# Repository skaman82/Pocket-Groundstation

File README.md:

# Pocket-Groundstation
The Pocket-Groundstation is a mini ground station that will accept any Fatshark module.</br> 
<strong>Project updates</strong> > https://github.com/skaman82/Pocket-Groundstation/blob/master/updates.md

<b>Features:</b></br>
• takes 2S to 4S voltage</br>
• 3,5mm AV output</br>
• RJ45 output for power+AV (only one wire to goggles) - constant 8V output on any power source </br>
• Powerswitch</br>
• Build-in DVR</br>
• Automatical switching between DVR output (to adjust settings or review footage) or direct module output</br>
• Low-voltage alarm and cell autodetection (adjustable via OLED, so it can work with lipo or li-ion batteries)</br>
• DRV-control via OLED (Eachine Pro DVR)</br>
• RSSI/Channel-information and DVR-Autostart (only with True-D module with 3.7D firmware)</br>
</br>

If you want to join the project or contribute, you are very welcome to do so!</br></br>

<b>Parts:</b></br>
• 3D-Printed Parts </br>
or order them here: </br>
https://www.shapeways.com/product/CZG7FD8B4/pocketgroundstation-module-insert</br>
https://www.shapeways.com/product/DPKJJELEF/pocketgroundstation-case-side-cover</br>
https://www.shapeways.com/product/GCXG232QY/pocketgroundstation-case</br>
</br>
</br>
• PCBs (you can order them with the provided Gerber files in the PCB Folder at http://jlcpcb.com or other vendors) </br>
• M3 inserts (https://de.aliexpress.com/item/100-teile-los-messingeinsatz-M2-M2-5-M3-Durch-gewinde-messing-gewindebuchse-r-ndelmuttern-f-r/32840519444.html) </br>
• Tripod 1/4" Insert: (https://de.aliexpress.com/item/20Pcs-M3-M4-M5-M6-M8-Zinc-Plated-Carbon-Steel-Knurled-Nuts-Rivnut-Flat-Head-Threaded/32812028855.html)</br>
• Eachine PRO DVR </br>
• Arduino Pro Mini (https://de.aliexpress.com/item/1PCS-new-version-1pcs-ATMEGA328P-Pro-Mini-328-Mini-ATMEGA328-5V-16MHz-for-arduino/32830465958.html?spm=a2g0s.9042311.0.0.30d64c4d7417Km)</br>
• 5V Buzzer</br>
• 3-35V to 1.2-30V Step up/down (https://de.aliexpress.com/item/DC-DC-Auto-Boost-Buck-Step-Up-Step-Down-Converter-Module-Solar-Voltage-LM2577-Module/32829391285.html?spm=a2g0s.9042311.0.0.758f4c4daLX5db)</br>
• DC 5.5x2.5 PCB socket (https://de.aliexpress.com/item/10pcs-DC-005-Black-DC-Power-Jack-Socket-Connector-DC005-5-5-2-1mm-2-1/32361314769.html)</br>
• 3.5mm PCB socket (PJ-320D) (https://de.aliexpress.com/item/10pcs-lot-3-5-headphone-jack-audio-jack-PJ-320D-4-pin-SMD-MP3-Accessories-PJ320D/32439357849.html)</br>
• RJ45 PCB socket (RJ45 MOLEX 0446200002/RJ45 MOLEX 0446200001)</br>
• I2C OLED Display 1.3" (https://de.aliexpress.com/item/1-3-Inch-1-3-White-OLED-LCD-4PIN-Display-Module-IIC-I2C-Interface-128x64-for/32837066822.html?spm=a2g0s.9042311.0.0.758f4c4daLX5db)</br>
• PWM video switch (https://de.aliexpress.com/item/2015-Mini-2-Ways-Video-Switcher-Module-2-Channels-Video-Switch-Unit-for-FPV/32552115472.html?spm=a2g0s.9042311.0.0.27424c4dOGX5bp)</br>
• Diode (SMD S1A)</br>
• Resistors 1206 (4.7K / 18K / 220 Ohm)</br>
• Red 3mm LED</br>
• Tactile buttons (3x) (https://de.aliexpress.com/item/100-st-cke-6-6-7mm-Licht-touch-schalter-DIP4-ON-OFF-Tactile-Push-button-micro/32846526815.html?spm=a2g0s.9042311.0.0.758f4c4daLX5db)</br>
• Power switch (https://de.aliexpress.com/item/10Pcs-AC-125V-12A-250V-10A-SPST-2-Pin-2-Position-Mini-Marine-Boat-Switches-Rocker/32830066263.html?spm=a2g0s.9042311.0.0.27424c4dOGX5bp)</br>
• 5V 2A BEC (Diatone)</br>
• RJ45 TBS Tango Cable </br>
• Optional: 3.5mm AV Cable</br>
• Optional: Capacitator (470uF 25V)</br>

# The Build

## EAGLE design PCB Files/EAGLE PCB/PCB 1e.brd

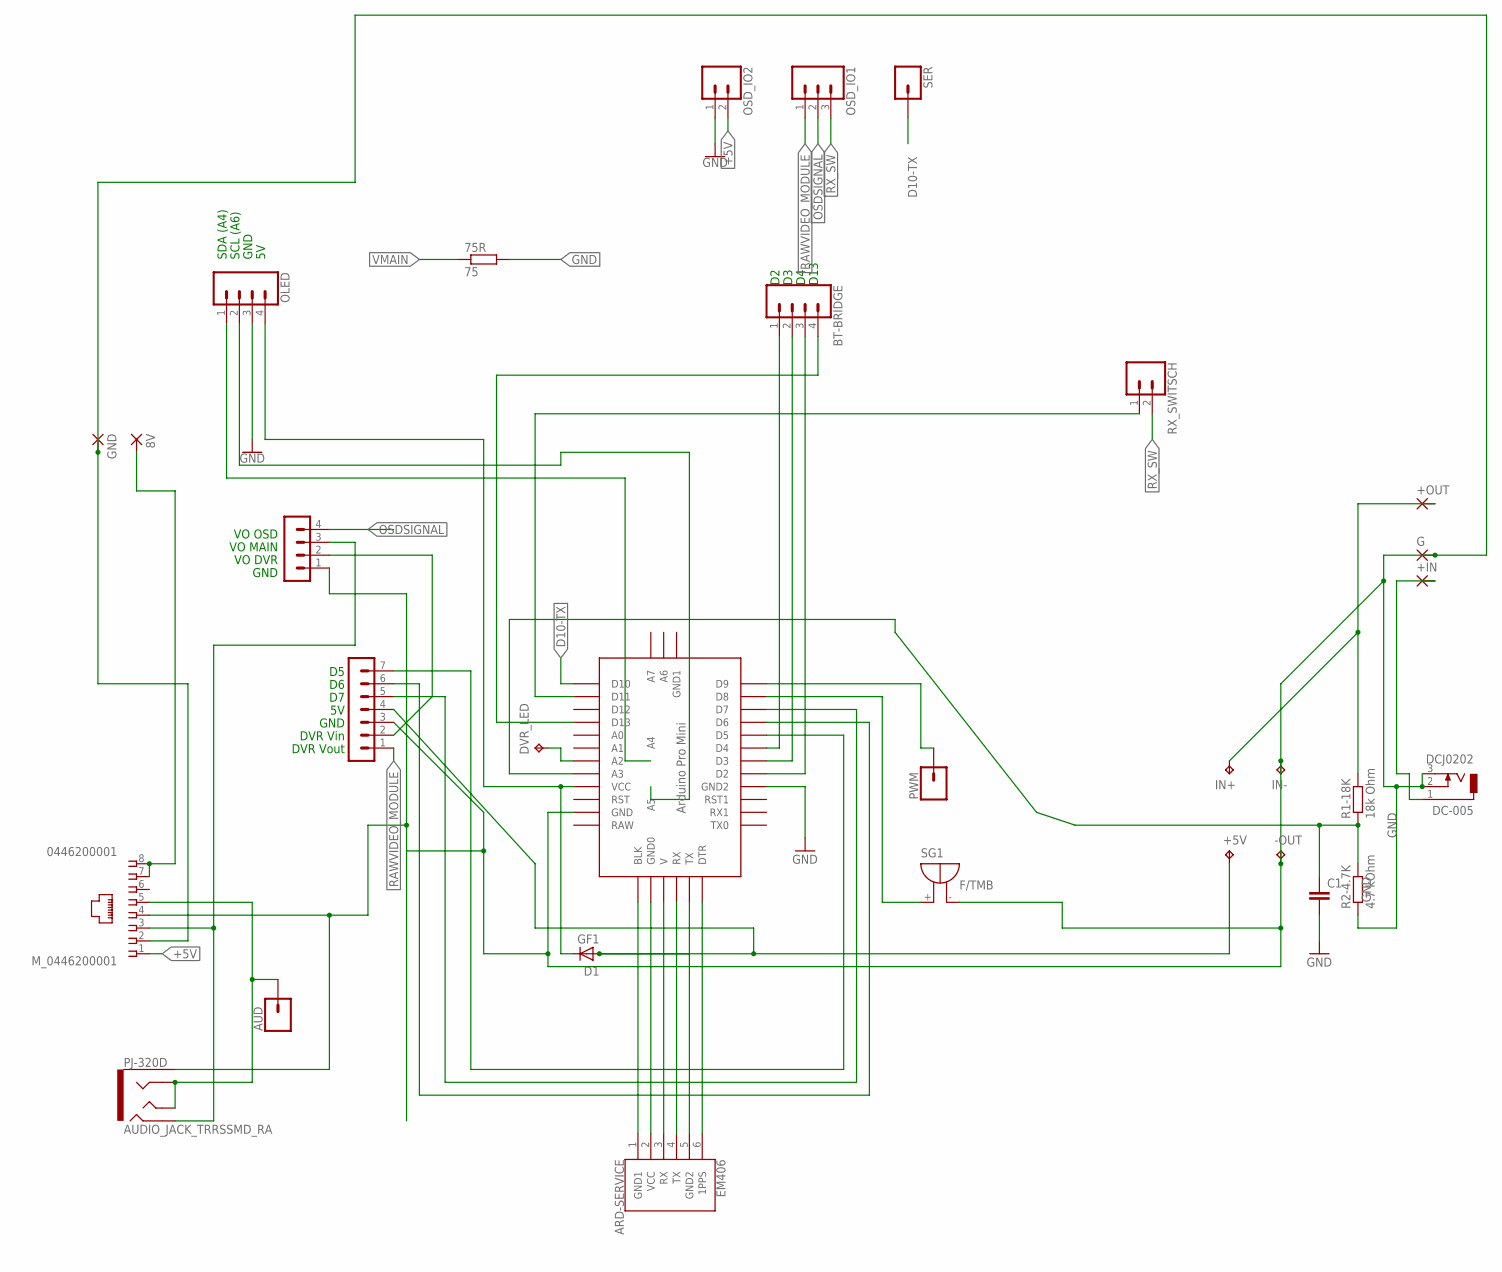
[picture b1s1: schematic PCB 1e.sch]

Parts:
8V: 2,54/1,1
75R: 75; R0603
+5V: TPTP20SQ; TP20SQ
+IN: 2,54/1,1
+OUT: 2,54/1,1
-OUT: TPTP20SQ; TP20SQ
ARD-SERVICE: EM406; 1X06-1MM
AUD: CONN_01; 1X01
BT-BRIDGE: CONN_04; 1X04
C1: C-EUC1206K; C1206K
D1: GF1; SMA-DO214AC
DC-005: DCJ0202
DVR_LED: TPTP20SQ; TP20SQ
G: 2,54/1,1
GND: 2,54/1,1
IN+: TPTP20SQ; TP20SQ
IN-: TPTP20SQ; TP20SQ
MODULE-IO: MA07-1
M_0446200001: 0446200001
OLED: CONN_04; 1X04
OSD_IO1: CONN_03; 1X03
OSD_IO2: CONN_02; 1X02
PJ-320D: AUDIO_JACK_TRRSSMD_RA; AUDIO_JACK_3.5MM_TRRS_SMD_RA
PWM: CONN_01; 1X01
R1-18K: 18k Ohm; M1206
R2-4.7K: 4.7 kOhm; M1206
RX_SWITSCH: CONN_02; 1X02
SER: CONN_01; 1X01
SG1: F/TMB
U$1: ABK-PRO-MINI
V-IO: MA04-1

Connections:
5VPROTECTED: D1.K (C), OLED.4, U$1.VCC
8V: 8V.1, M_0446200001.7, M_0446200001.8
+: +IN.1, DC-005.1
+5V: +5V.TP, D1.A, MODULE-IO.4, M_0446200001.1, OSD_IO2.2
AUDIO: AUD.1, M_0446200001.5, PJ-320D.RING1, PJ-320D.TIP
BUTTON1: BT-BRIDGE.3, U$1.D2
BUTTON2: BT-BRIDGE.2, U$1.D3
BUTTON3: BT-BRIDGE.1, U$1.D4
BUZZER: SG1.+, U$1.D8
D5: MODULE-IO.7, U$1.D5
D6: MODULE-IO.6, U$1.D6
D7: MODULE-IO.5, U$1.D7
D9PWM: PWM.1, U$1.D9
D10-TX: SER.1, U$1.D10
D11-RX: RX_SWITSCH.1, U$1.D11
DVRVIDEO-IN: MODULE-IO.2, V-IO.2
GND: 75R.2, -OUT.TP, C1.2, DC-005.2, DC-005.3, G.1, GND.1, IN-.TP, MODULE-IO.3, M_0446200001.2, M_0446200001.4, OLED.3, OSD_IO2.1, PJ-320D.EARTH, R2-4.7K.1, SG1.-, U$1.GND, U$1.GND1 (GND2), V-IO.1
LED: BT-BRIDGE.4, U$1.D13
unnamed: DVR_LED.TP, U$1.A1 (A2)
unnamed: ARD-SERVICE.1 (GND1), U$1.BLK
unnamed: ARD-SERVICE.2 (VCC), U$1.G (GND0)
unnamed: ARD-SERVICE.3 (RX), U$1.5V (V)
unnamed: ARD-SERVICE.5 (GND2), U$1.TX01 (TX)
unnamed: ARD-SERVICE.6 (1PPS), U$1.DTR
OSDSIGNAL: OSD_IO1.2, V-IO.4
RAWVIDEO_MODULE: MODULE-IO.1, OSD_IO1.1
RX_SW: OSD_IO1.3, RX_SWITSCH.2
SCL: OLED.2, U$1.A5
SDA: OLED.1, U$1.A4
V: ARD-SERVICE.4 (TX), U$1.RX01 (RX)
VCC: +OUT.1, IN+.TP, R1-18K.2
VMAIN: 75R.1, M_0446200001.3, PJ-320D.RING2, V-IO.3
VSENS: C1.1, R1-18K.1, R2-4.7K.2, U$1.A0 (A3)

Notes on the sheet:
VO OSD
VO MAIN
VO DVR
GND
DVR Vin
DVR Vout
SDA (A4)
SCL (A6)
D13

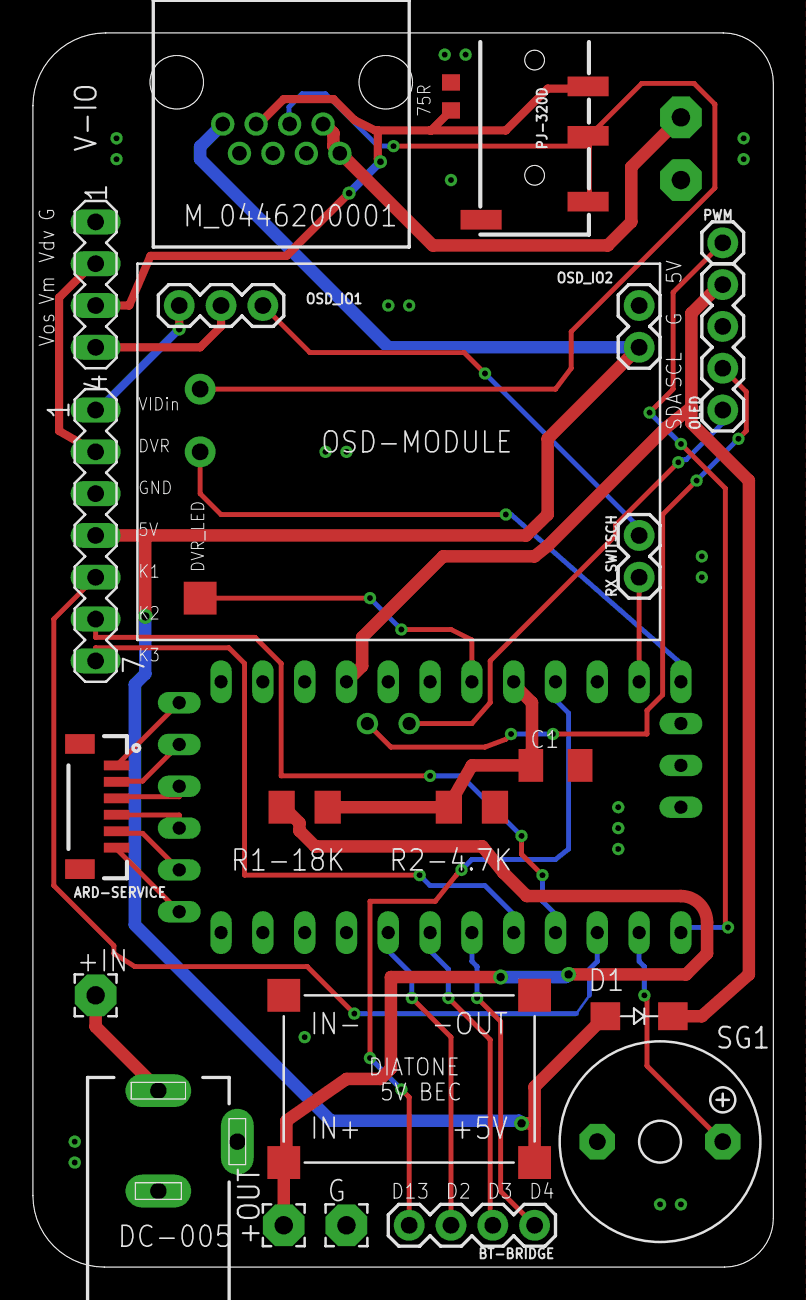
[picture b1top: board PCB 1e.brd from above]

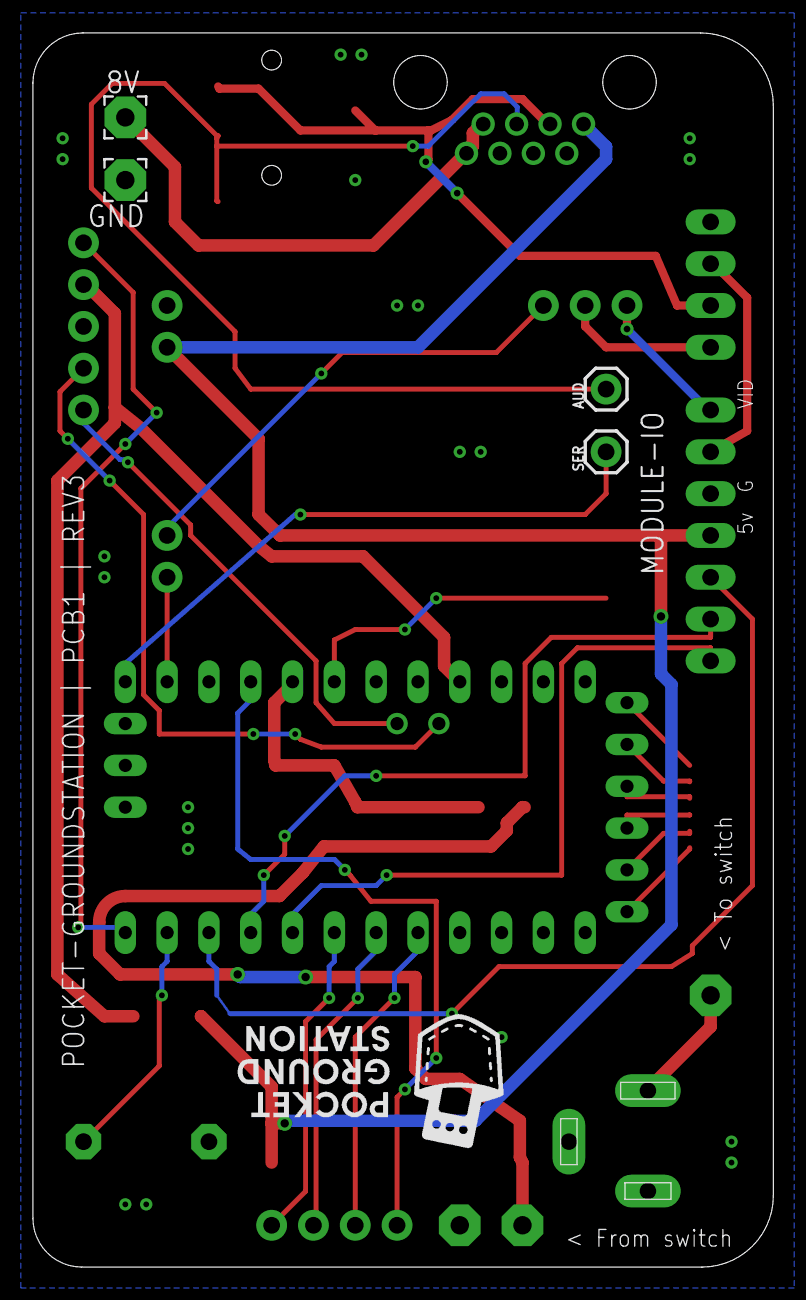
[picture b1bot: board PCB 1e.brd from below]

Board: 2 copper layers, 45.0 x 75.0 mm, 31 parts (4 on the bottom side), 33 nets.

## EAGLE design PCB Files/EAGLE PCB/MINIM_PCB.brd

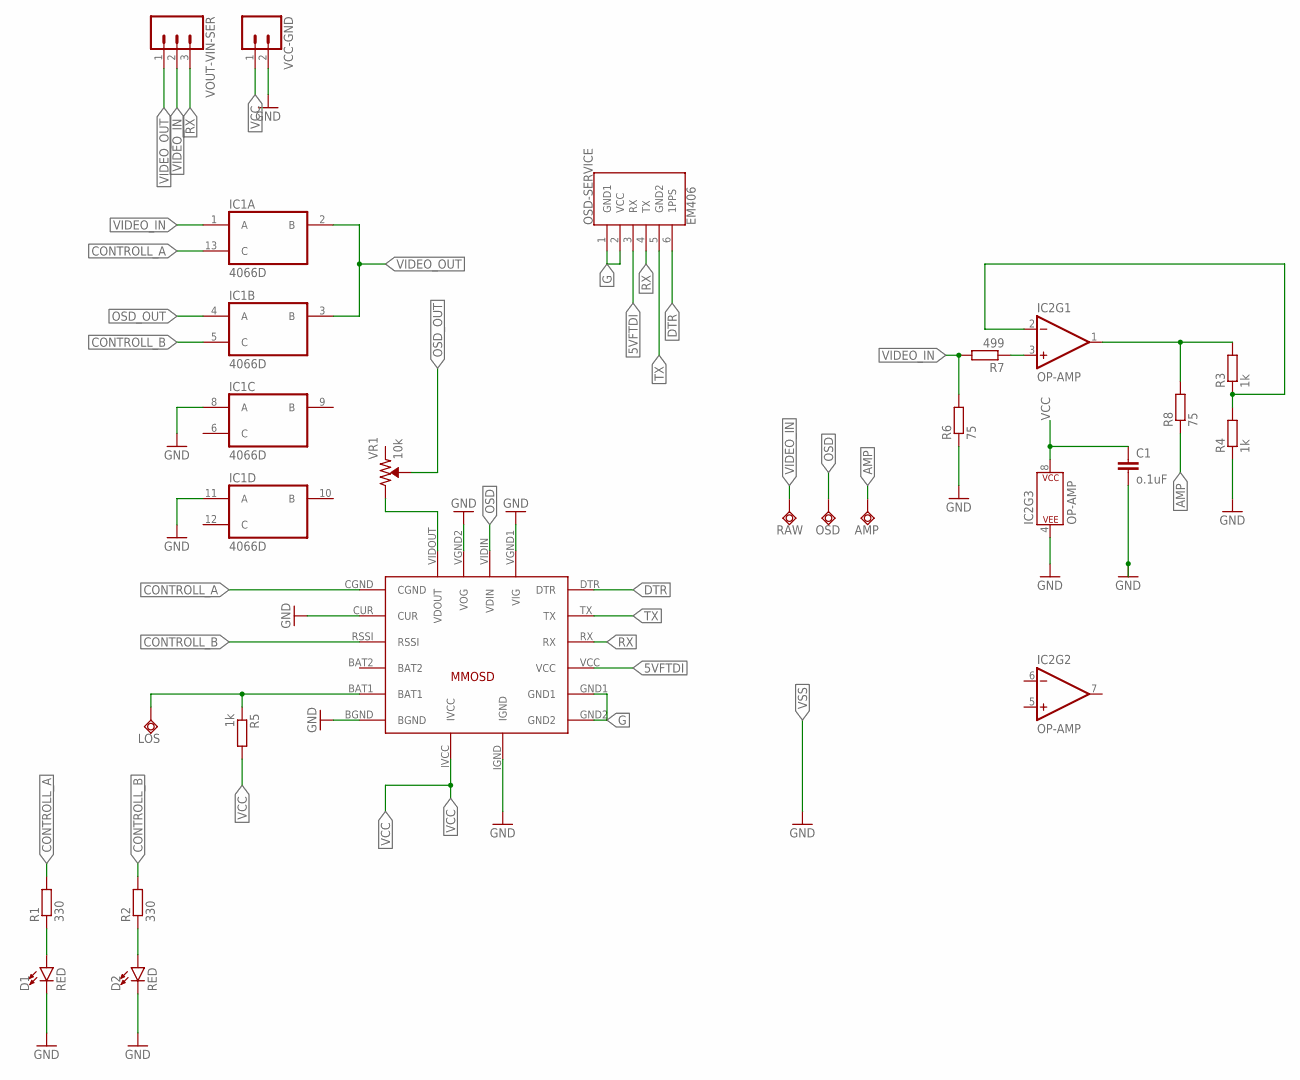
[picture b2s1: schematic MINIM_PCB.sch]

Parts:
AMP: TPSQTP13SQ; TP13SQ
C1: o.1uF; C0603K
D1, D2: RED; LED-1206
IC1: 4066D; SO14
IC2: OP-AMP; SO08
LOS: TPSQTP13SQ; TP13SQ
MINIMOSD: MICROMINIMOSDPWR; MMOSDNVDVID
OSD: TPSQTP13SQ; TP13SQ
OSD-SERVICE: EM406; 1X06-1MM
R1, R2: 330; R0603
R3, R4, R5: 1k; R0603
R6, R8: 75; R0603
R7: 499; R0603
RAW: TPSQTP13SQ; TP13SQ
VCC-GND: CONN_02; 1X02
VOUT-VIN-SER: CONN_03; 1X03
VR1: 10k; TRIMPOT-SMD-3MM-CLOSED

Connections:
5VFTDI: MINIMOSD.VCC, OSD-SERVICE.3 (RX)
75: IC2.1 (OUT), R3.2, R8.2
AMP: AMP.TP, R8.1
BAT2: MINIMOSD.BAT2
CONTROLL_A: IC1.13 (C), MINIMOSD.CGND, R1.2
CONTROLL_B: IC1.5 (C), MINIMOSD.RSSI, R2.2
DTR: MINIMOSD.DTR, OSD-SERVICE.6 (1PPS)
G: MINIMOSD.GND1, MINIMOSD.GND2, OSD-SERVICE.1 (GND1), OSD-SERVICE.2 (VCC)
GND: C1.2, D1.C, D2.C, IC1.8 (A), IC1.11 (A), IC2.4 (P$V-), MINIMOSD.BGND, MINIMOSD.CUR, MINIMOSD.IGND, MINIMOSD.VGND1 (VIG), MINIMOSD.VGND2 (VOG), R4.1, R6.1, VCC-GND.2
unnamed: D2.A, R2.1
unnamed: D1.A, R1.1
unnamed: LOS.TP, MINIMOSD.BAT1, R5.1
unnamed: IC2.2 (-IN), R3.1, R4.2
unnamed: MINIMOSD.VIDOUT (VDOUT), VR1.3 (CW)
OSD: MINIMOSD.VIDIN (VDIN), OSD.TP
OSD_OUT: IC1.4 (A), VR1.2 (WIPER)
RX: MINIMOSD.RX, OSD-SERVICE.4 (TX), VOUT-VIN-SER.3
TX: MINIMOSD.TX, OSD-SERVICE.5 (GND2)
VCC: C1.1, IC1.14 (VDD), IC2.8 (P$V+), MINIMOSD.IVCC, R5.2, VCC-GND.1
VIDEO_IN: IC1.1 (A), R6.2, R7.2, RAW.TP, VOUT-VIN-SER.2
VIDEO_OUT: IC1.2 (B), IC1.3 (B), VOUT-VIN-SER.1
VIDIN_AMP: IC2.3 (+IN), R7.1
VSS: IC1.7 (VSS)

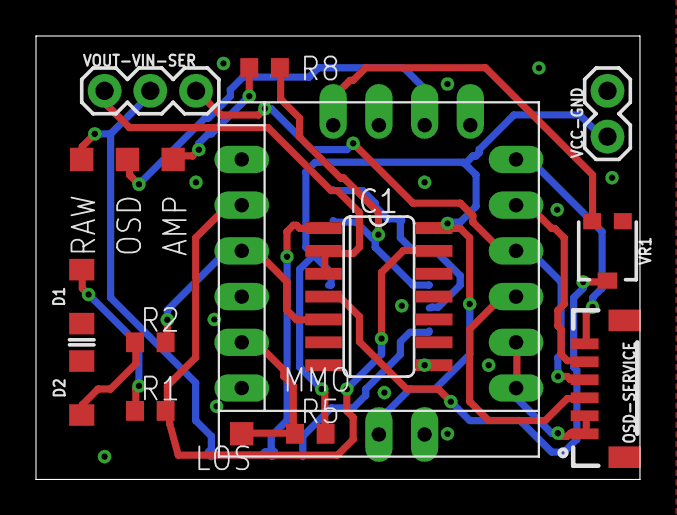
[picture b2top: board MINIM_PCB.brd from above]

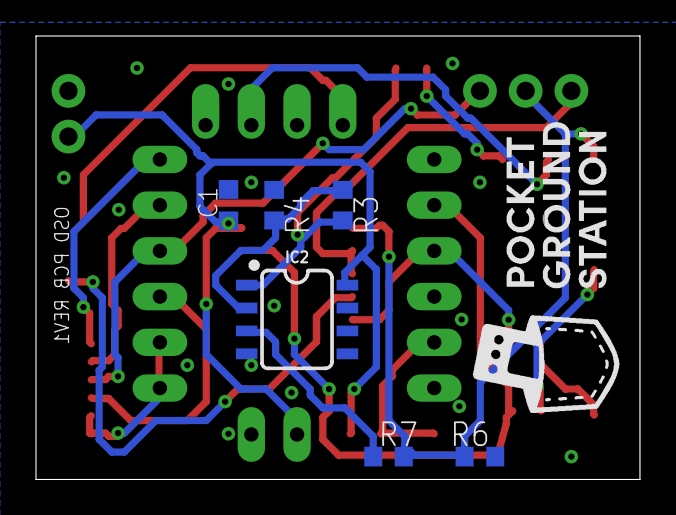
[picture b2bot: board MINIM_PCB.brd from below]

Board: 2 copper layers, 33.6 x 24.6 mm, 22 parts (6 on the bottom side), 21 nets.

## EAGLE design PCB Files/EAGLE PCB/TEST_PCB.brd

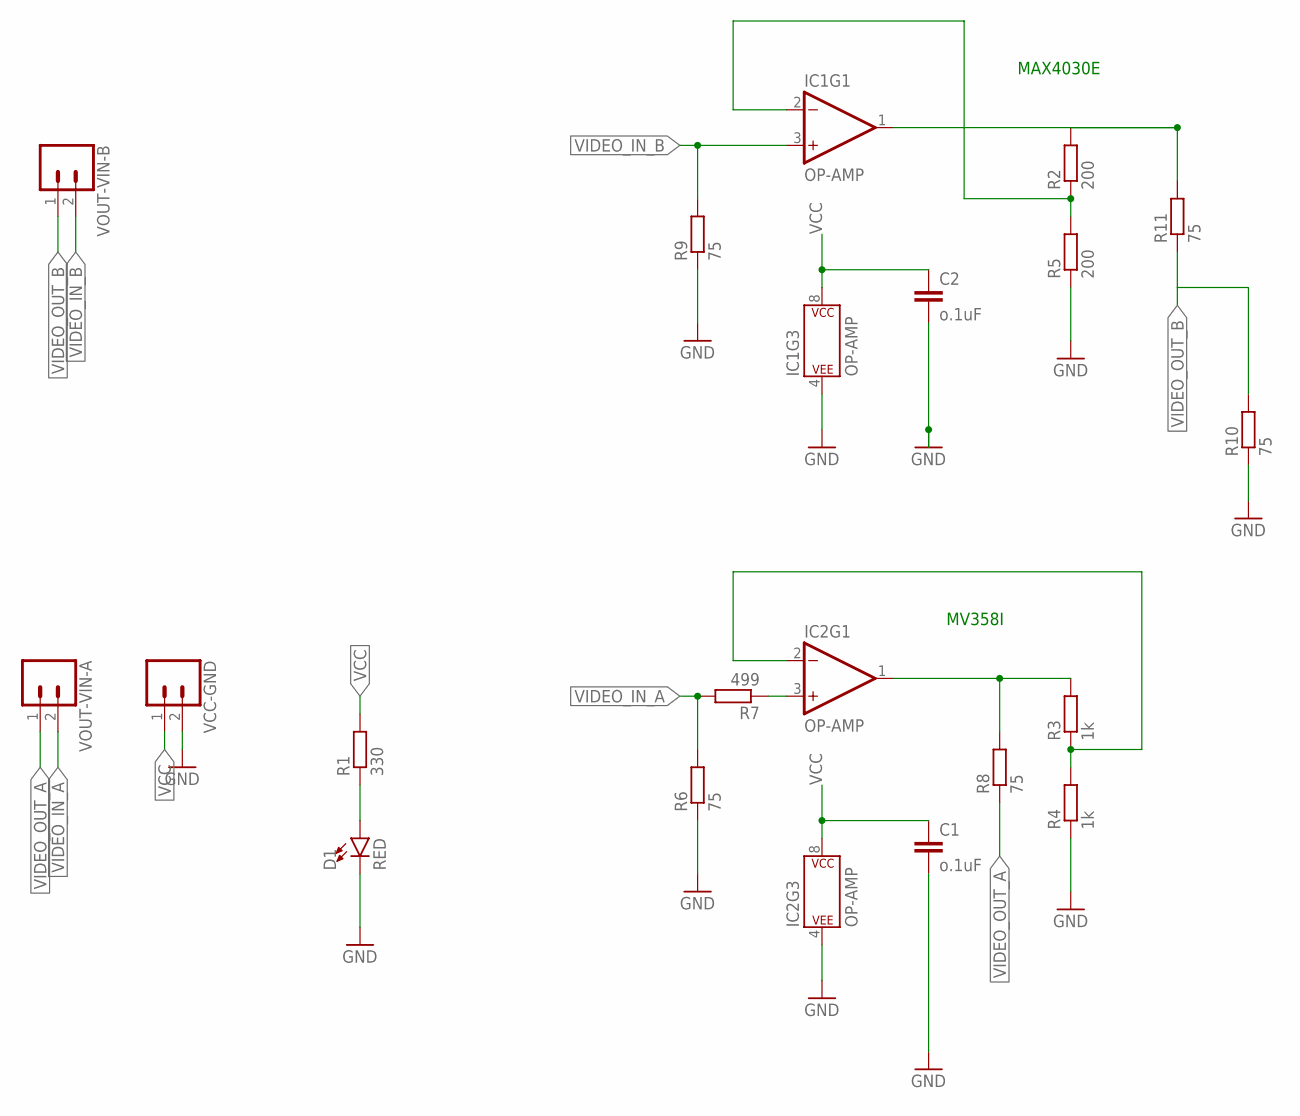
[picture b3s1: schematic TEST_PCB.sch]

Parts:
C1, C2: o.1uF; C0603K
D1: RED; LED-1206
IC1, IC2: OP-AMP; SO08
R1: 330; R0603
R2, R5: 200; R0603
R3, R4: 1k; R0603
R6, R8, R9, R10, R11: 75; R0603
R7: 499; R0603
VCC-GND: CONN_02; 1X02
VOUT-VIN-A: CONN_02; 1X02
VOUT-VIN-B: CONN_02; 1X02

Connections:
1: IC1.1 (OUT), R2.2, R11.2
75: IC2.1 (OUT), R3.2, R8.2
GND: C1.2, C2.2, D1.C, IC1.4 (P$V-), IC2.4 (P$V-), R4.1, R5.1, R6.1, R9.1, R10.1, VCC-GND.2
unnamed: IC1.2 (-IN), R2.1, R5.2
unnamed: D1.A, R1.1
unnamed: IC2.2 (-IN), R3.1, R4.2
unnamed: IC2.3 (+IN), R7.1
VCC: C1.1, C2.1, IC1.8 (P$V+), IC2.8 (P$V+), R1.2, VCC-GND.1
VIDEO_IN_A: R6.2, R7.2, VOUT-VIN-A.2
VIDEO_IN_B: IC1.3 (+IN), R9.2, VOUT-VIN-B.2
VIDEO_OUT_A: R8.1, VOUT-VIN-A.1
VIDEO_OUT_B: R10.2, R11.1, VOUT-VIN-B.1

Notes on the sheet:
MAX4030E
MV358I

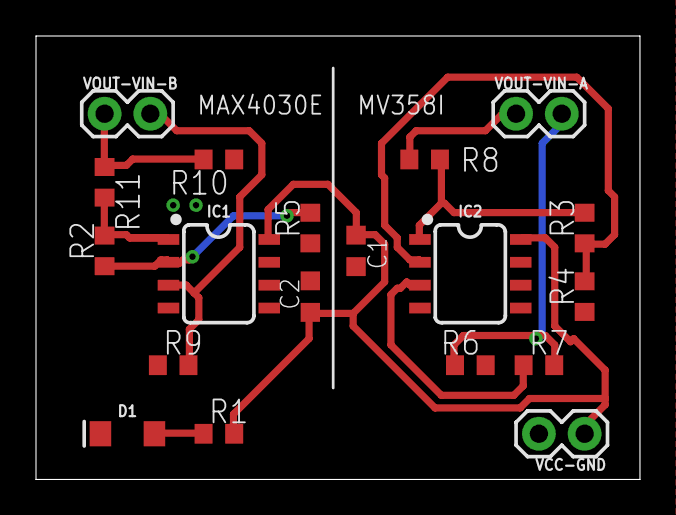
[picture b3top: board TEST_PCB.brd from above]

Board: 2 copper layers, 33.6 x 24.6 mm, 19 parts (0 on the bottom side), 12 nets.

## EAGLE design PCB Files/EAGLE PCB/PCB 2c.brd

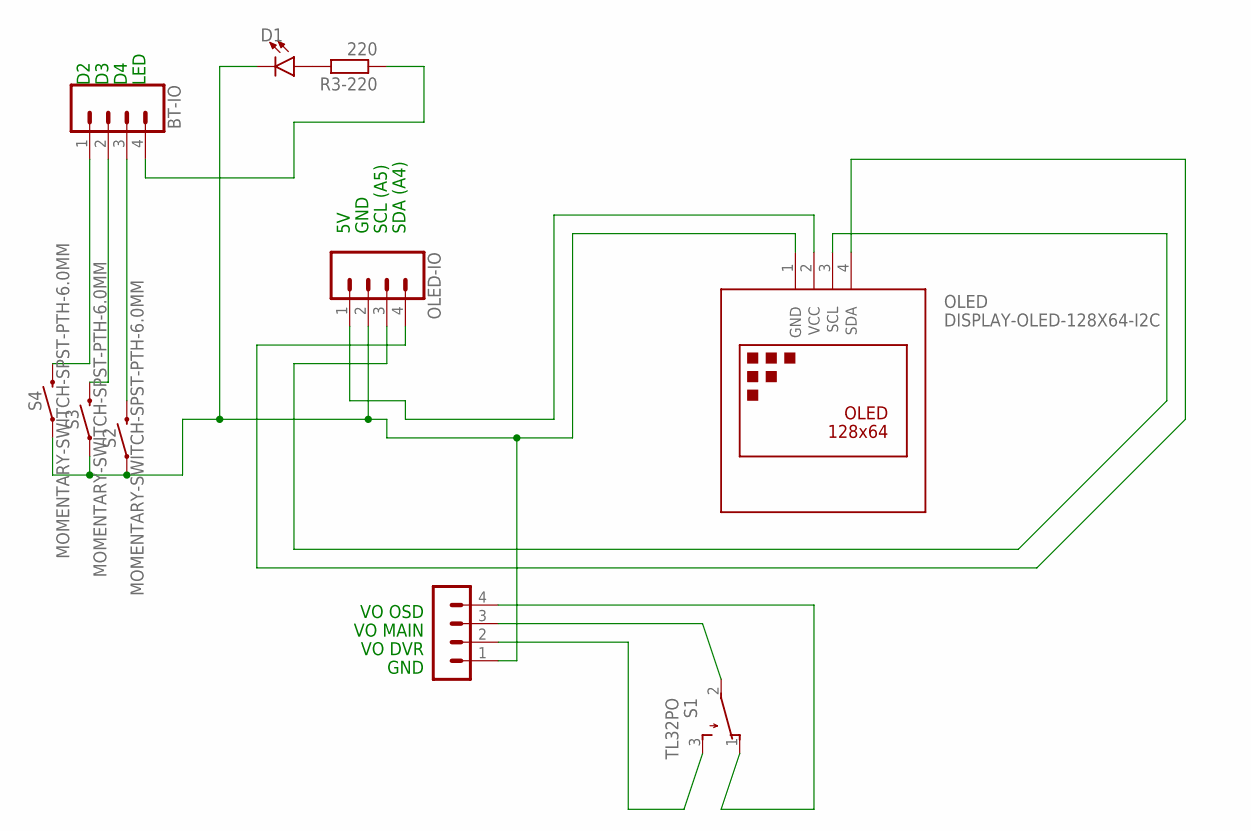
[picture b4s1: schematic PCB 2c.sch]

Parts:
BT-IO: CONN_04; 1X04
D1: LED3MM; LED_3MM
IO3: MA04-1
OLED: DISPLAY-OLED-128X64-I2C
OLED-IO: CONN_04; 1X04
R3-220: 220; R1206
S1: TL32PO; TL3XPO
S2, S3, S4: MOMENTARY-SWITCH-SPST-PTH-6.0MM; TACTILE_SWITCH_PTH_6.0MM

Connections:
GND: D1.K (C), IO3.1, OLED.1 (GND), OLED-IO.2, S2.1, S3.1, S4.1
unnamed: D1.A, R3-220.2
unnamed: BT-IO.1, S4.3 (2)
unnamed: IO3.3, S1.2
unnamed: OLED.2 (VCC), OLED-IO.1
unnamed: BT-IO.4, R3-220.1
unnamed: OLED.4 (SDA), OLED-IO.4
unnamed: OLED.3 (SCL), OLED-IO.3
unnamed: IO3.2, S1.3 (S)
unnamed: BT-IO.2, S3.3 (2)
unnamed: BT-IO.3, S2.3 (2)
VIDOUT: IO3.4, S1.1 (O)

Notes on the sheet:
VO OSD
VO MAIN
VO DVR
GND
SDA (A4)
SCL (A5)
LED

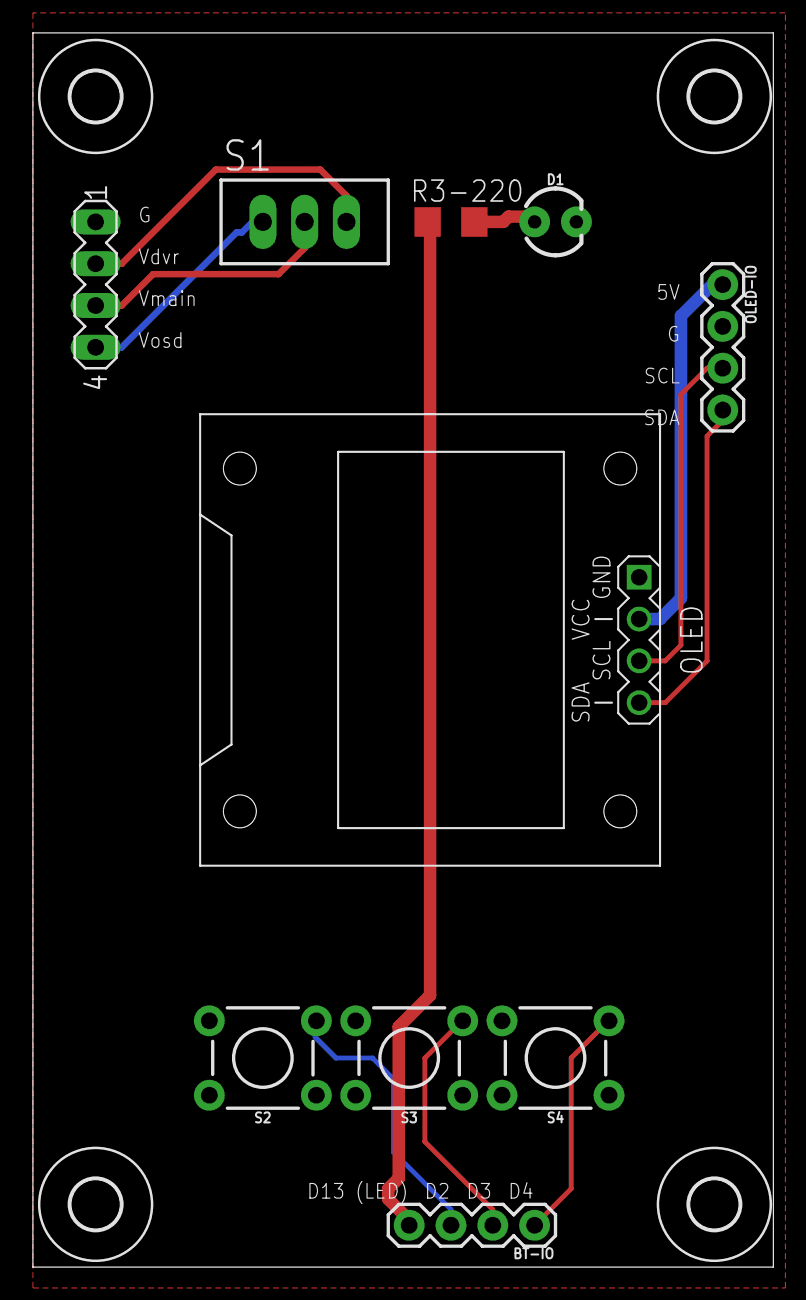
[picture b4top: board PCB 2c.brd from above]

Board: 2 copper layers, 45.0 x 75.0 mm, 14 parts (0 on the bottom side), 12 nets.

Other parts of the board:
U$2, U$3, U$4, U$5: 3,0

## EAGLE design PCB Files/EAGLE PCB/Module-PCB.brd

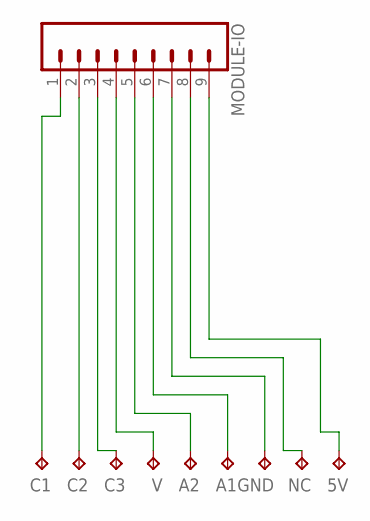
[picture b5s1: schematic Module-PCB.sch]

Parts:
5V: TPTP20SQ; TP20SQ
A1, A2: TPTP20SQ; TP20SQ
C1, C2, C3: TPTP20SQ; TP20SQ
GND: TPTP20SQ; TP20SQ
MODULE-IO: CONN_09; 1X09
NC: TPTP20SQ; TP20SQ
V: TPTP20SQ; TP20SQ

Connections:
3: C3.TP, MODULE-IO.3
GND: GND.TP, MODULE-IO.7
unnamed: C1.TP, MODULE-IO.1
unnamed: C2.TP, MODULE-IO.2
unnamed: MODULE-IO.4, V.TP
unnamed: A2.TP, MODULE-IO.5
unnamed: A1.TP, MODULE-IO.6
unnamed: MODULE-IO.8, NC.TP
unnamed: 5V.TP, MODULE-IO.9

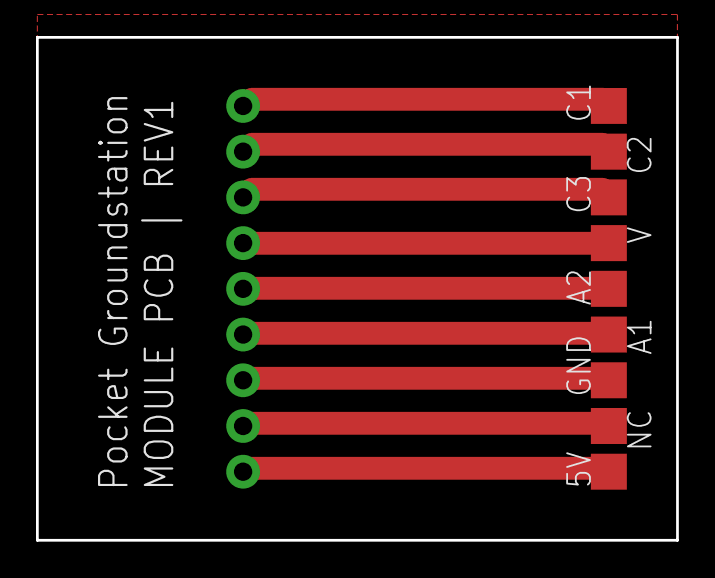
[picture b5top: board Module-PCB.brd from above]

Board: 2 copper layers, 35.6 x 27.9 mm, 10 parts (1 on the bottom side), 9 nets.

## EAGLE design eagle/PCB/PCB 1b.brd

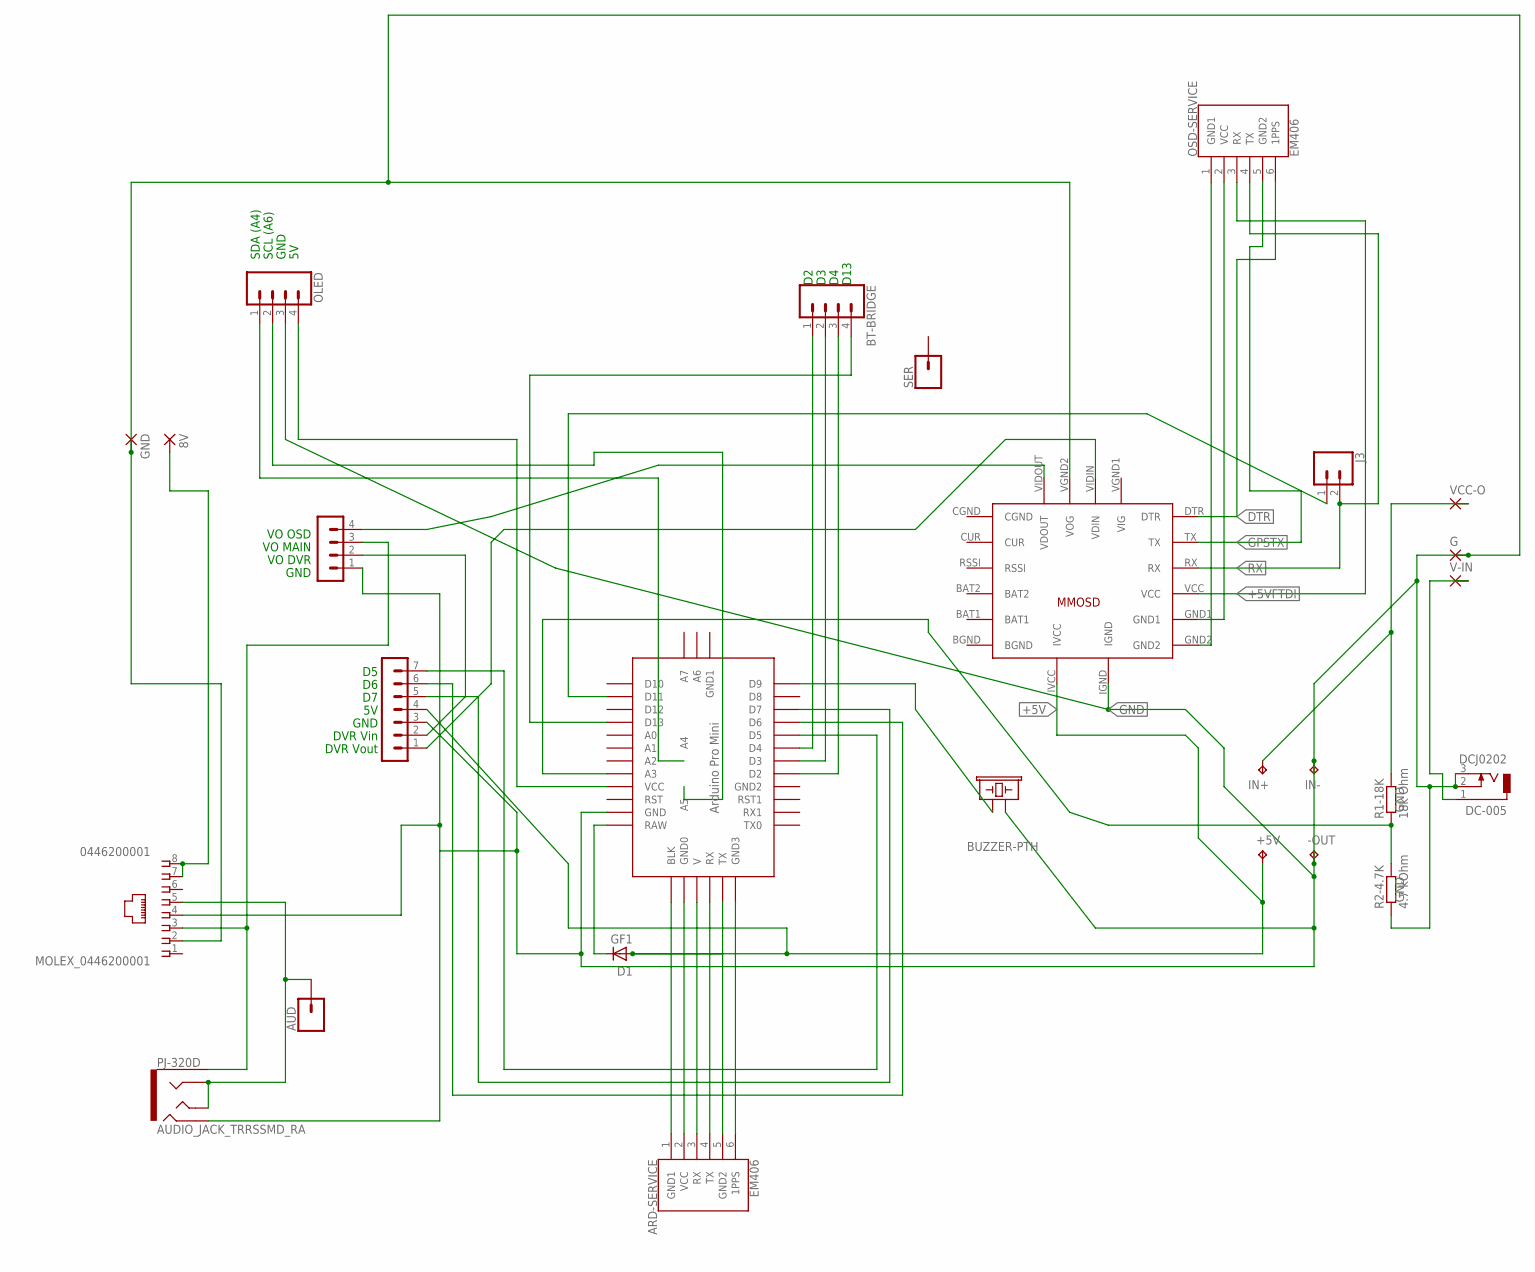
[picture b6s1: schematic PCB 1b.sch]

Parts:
8V: 2,54/1,1
+5V: TPTP20SQ; TP20SQ
-OUT: TPTP20SQ; TP20SQ
ARD-SERVICE: EM406; 1X06-1MM
AUD: CONN_01; 1X01
BT-BRIDGE: CONN_04; 1X04
BUZZ: BUZZER-PTH; BUZZER-12MM
D1: GF1; SMA-DO214AC
DC-005: DCJ0202
DVR/MODULE-IO: MA07-1
G: 2,54/1,1
GND: 2,54/1,1
IN+: TPTP20SQ; TP20SQ
IN-: TPTP20SQ; TP20SQ
J3: CONN_02; 1X02
MINIMOSD: MICROMINIMOSDPWR; MMOSDNVDVID
MOLEX_0446200001: 0446200001
OLED: CONN_04; 1X04
OSD-SERVICE: EM406; 1X06-1MM
PJ-320D: AUDIO_JACK_TRRSSMD_RA; AUDIO_JACK_3.5MM_TRRS_SMD_RA
R1-18K: 18k Ohm; M1206
R2-4.7K: 4.7 kOhm; M1206
SER: CONN_01; 1X01
U$1: ABK-PRO-MINI
V-IN: 2,54/1,1
V-IO: MA04-1
VCC-O: 2,54/1,1

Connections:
8V: 8V.1, MOLEX_0446200001.7, MOLEX_0446200001.8
+: DC-005.1, V-IN.1
+5V: +5V.TP, D1.A, DVR/MODULE-IO.4, MINIMOSD.IVCC
+5VFTDI: MINIMOSD.VCC, OSD-SERVICE.3 (RX)
AUDIO: AUD.1, MOLEX_0446200001.5, PJ-320D.RING1, PJ-320D.TIP
BAT1: MINIMOSD.BAT1
BAT2: MINIMOSD.BAT2
BGND: MINIMOSD.BGND
CGND: MINIMOSD.CGND
D5: DVR/MODULE-IO.7, U$1.D5
D6: DVR/MODULE-IO.6, U$1.D6
D7: DVR/MODULE-IO.5, U$1.D7
D10RX: J3.1, U$1.D11
DTR: MINIMOSD.DTR, OSD-SERVICE.6 (1PPS)
DVRVIDEO-IN: DVR/MODULE-IO.2, V-IO.2
GND: -OUT.TP, BUZZ.- (2), DC-005.2, DC-005.3, DVR/MODULE-IO.3, G.1, GND.1, IN-.TP, MINIMOSD.IGND, MINIMOSD.VGND2 (VOG), MOLEX_0446200001.2, MOLEX_0446200001.4, OLED.3, PJ-320D.RING2, R2-4.7K.1, U$1.GND, V-IO.1
GPSTX: MINIMOSD.TX, OSD-SERVICE.5 (GND2)
HP5: BT-BRIDGE.3, U$1.D2
HP6: BT-BRIDGE.1, U$1.D4
unnamed: BT-BRIDGE.2, U$1.D3
unnamed: OLED.4, U$1.VCC
unnamed: MINIMOSD.GND1, OSD-SERVICE.2 (VCC)
unnamed: D1.K (C), U$1.RAW
unnamed: MINIMOSD.GND2, OSD-SERVICE.1 (GND1)
unnamed: BT-BRIDGE.4, U$1.D13
unnamed: BUZZ.+ (1), U$1.D9
unnamed: R1-18K.1, R2-4.7K.2, U$1.A0 (A3)
unnamed: ARD-SERVICE.1 (GND1), U$1.BLK
unnamed: ARD-SERVICE.2 (VCC), U$1.G (GND0)
unnamed: ARD-SERVICE.3 (RX), U$1.5V (V)
unnamed: ARD-SERVICE.5 (GND2), U$1.TX01 (TX)
unnamed: ARD-SERVICE.6 (1PPS), U$1.DTR (GND3)
OSDSIGNAL: MINIMOSD.VIDOUT (VDOUT), V-IO.4
RAWVIDEO_MODULE: DVR/MODULE-IO.1, MINIMOSD.VIDIN (VDIN)
RX: J3.2, MINIMOSD.RX, OSD-SERVICE.4 (TX)
SCL: OLED.2, U$1.A5
SDA: OLED.1, U$1.A4
V: ARD-SERVICE.4 (TX), U$1.RX01 (RX)
VCC: IN+.TP, R1-18K.2, VCC-O.1
VMAIN: MOLEX_0446200001.3, PJ-320D.EARTH, V-IO.3

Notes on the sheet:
VO OSD
VO MAIN
VO DVR
GND
DVR Vin
DVR Vout
SDA (A4)
SCL (A6)
D13

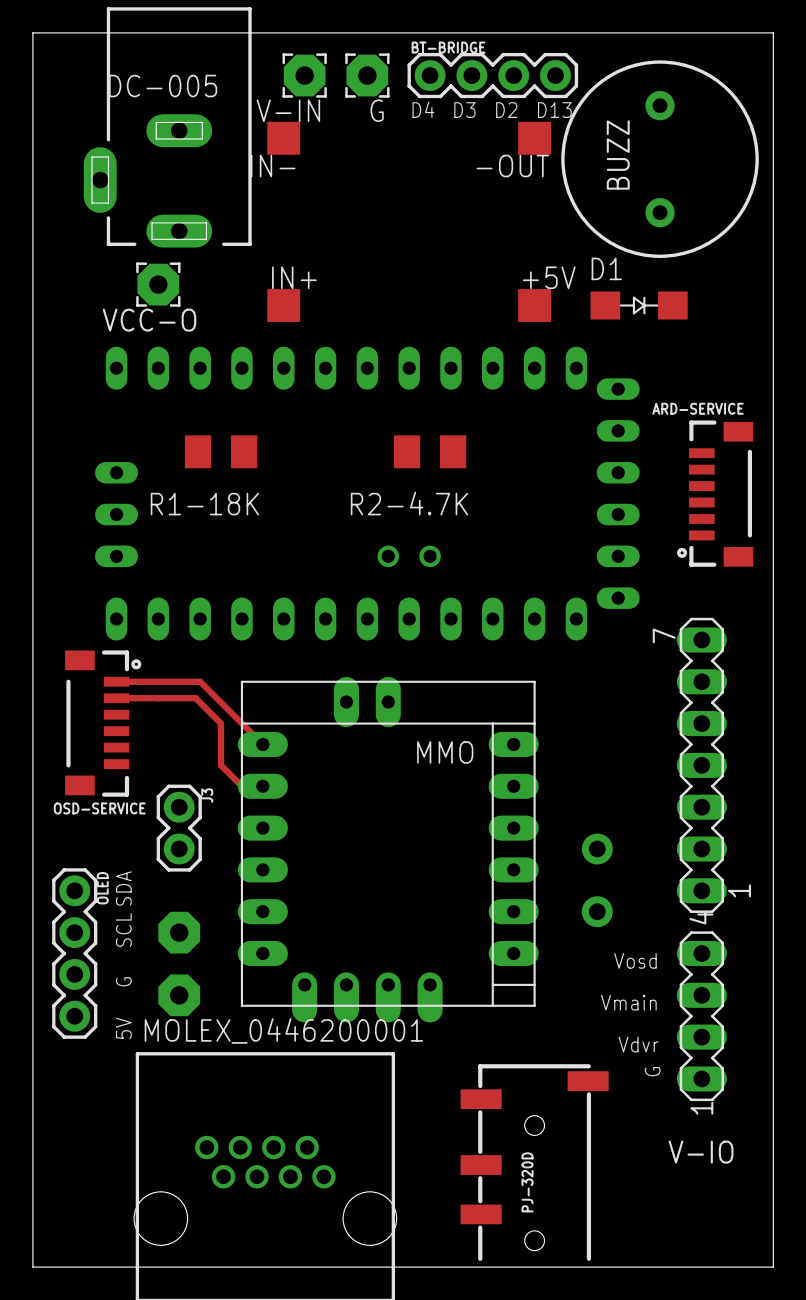
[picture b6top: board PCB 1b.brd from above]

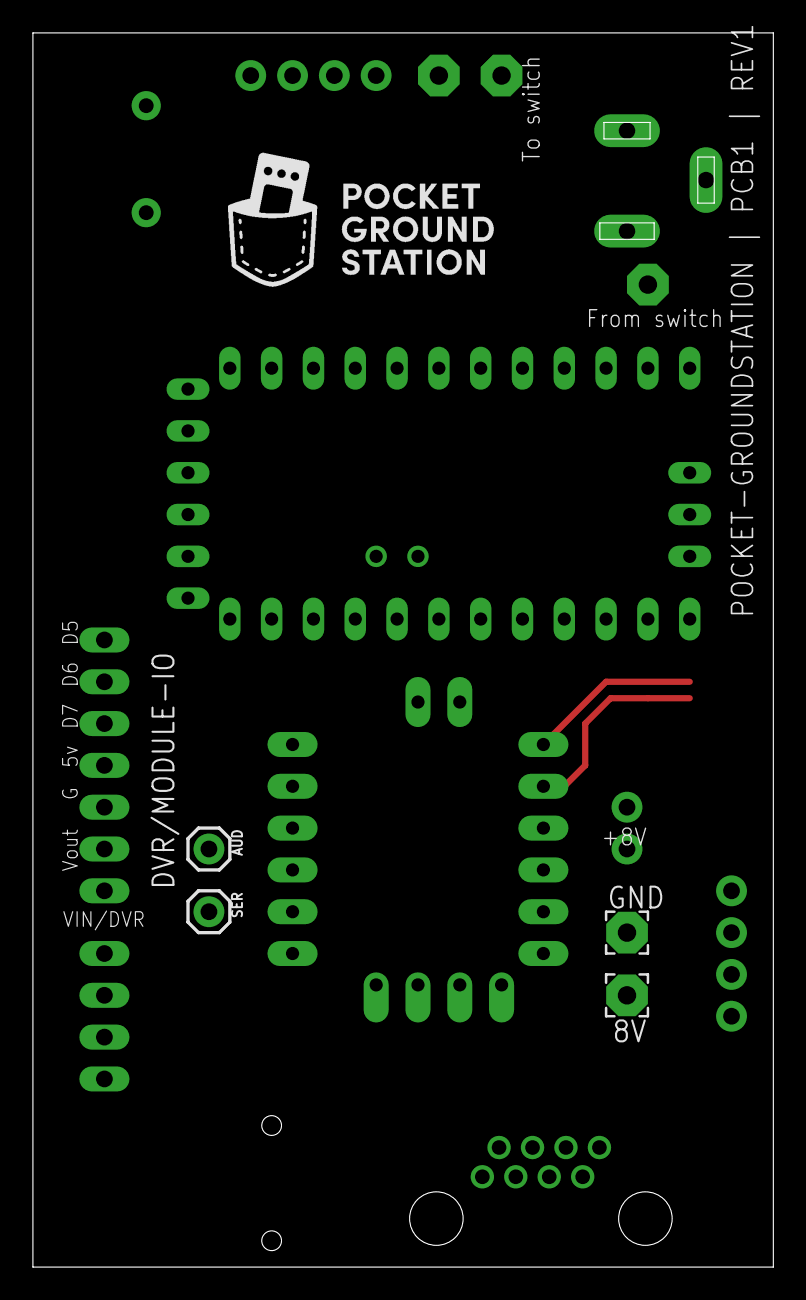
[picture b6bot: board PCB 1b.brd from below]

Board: 2 copper layers, 45.0 x 75.0 mm, 27 parts (4 on the bottom side), 36 nets.

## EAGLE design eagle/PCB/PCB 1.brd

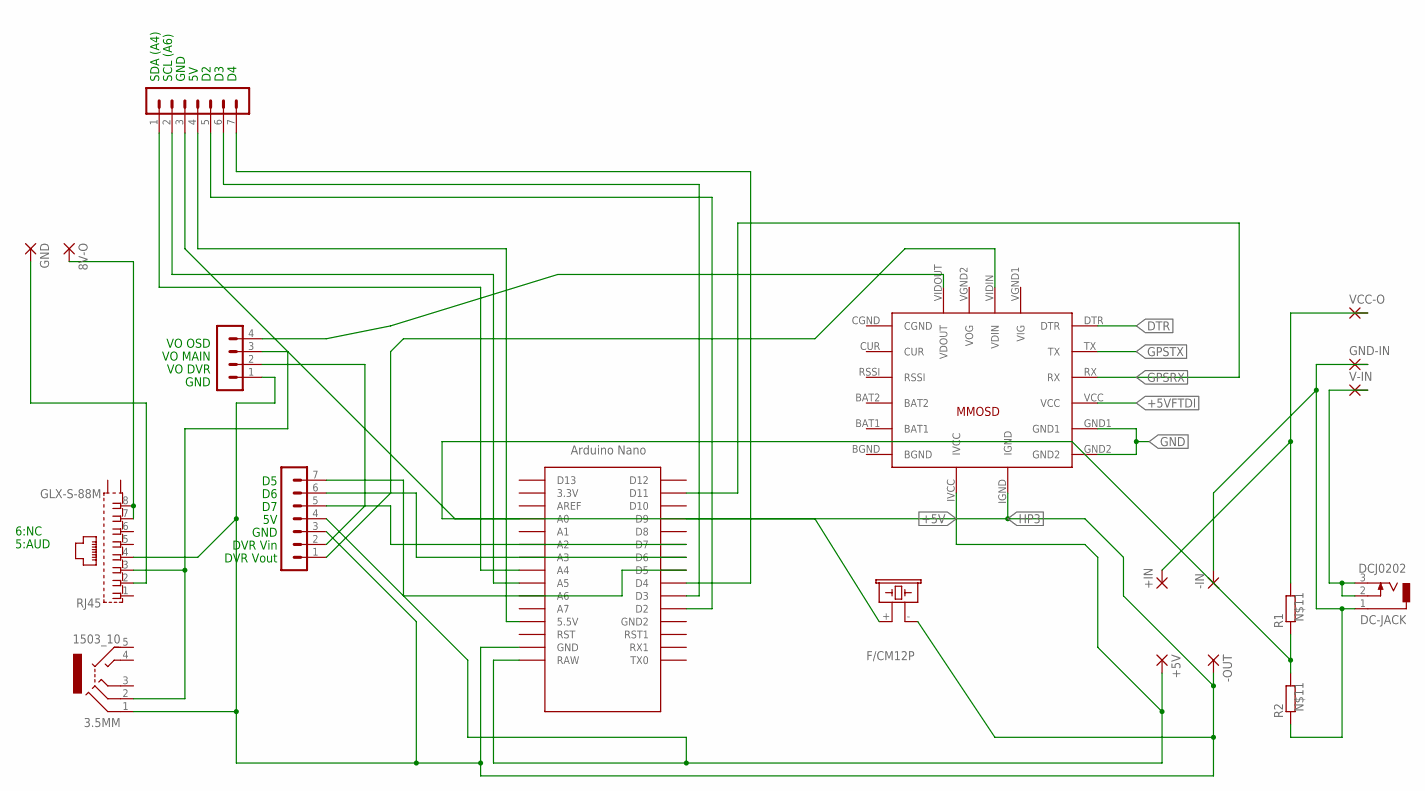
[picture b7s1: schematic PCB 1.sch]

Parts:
3.5MM: 1503_10
8V-O: 2,54/1,1
+5V: SMD2; SMD1,27-2,54
+IN: SMD2; SMD1,27-2,54
-IN: SMD2; SMD1,27-2,54
-OUT: SMD2; SMD1,27-2,54
ADRUINO-NANO: NANO
BUZZ: F/CM12P
DC-JACK: DCJ0202
GND: 2,54/1,1
GND-IN: 2,54/1,1
IO1, IO2: MA07-1
IO3: MA04-1
MINIMOSD: MICROMINIMOSDPWR; MMOSDNVDVID
R1, R2: R0207/10; 0207/10
RJ45: GLX-S-88M
V-IN: 2,54/1,1
VCC-O: 2,54/1,1

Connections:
+5V: +5V.1, ADRUINO-NANO.RAW, IO1.4, MINIMOSD.IVCC
+5VFTDI: MINIMOSD.VCC
BAT1: MINIMOSD.BAT1
BAT2: MINIMOSD.BAT2
BGND: MINIMOSD.BGND
CGND: MINIMOSD.CGND
DTR: MINIMOSD.DTR
GND: MINIMOSD.GND1, MINIMOSD.GND2
GPSRX: ADRUINO-NANO.D11, MINIMOSD.RX
GPSTX: MINIMOSD.TX
HP1: ADRUINO-NANO.A4, IO2.1
HP2: ADRUINO-NANO.A5, IO2.2
HP3: 3.5MM.1, -OUT.1, ADRUINO-NANO.GND, BUZZ.- (2), IO1.3, IO2.3, IO3.1, MINIMOSD.IGND, RJ45.4
HP5: ADRUINO-NANO.D2, IO2.5
HP6: ADRUINO-NANO.D3, IO2.6
HP7: ADRUINO-NANO.D4, IO2.7
unnamed: ADRUINO-NANO.5V (5.5V), IO2.4
unnamed: ADRUINO-NANO.A0, R1.1, R2.2
unnamed: ADRUINO-NANO.D5, IO1.7
unnamed: DC-JACK.2, DC-JACK.3, V-IN.1
unnamed: 8V-O.1, RJ45.7, RJ45.8
unnamed: GND.1, RJ45.2
unnamed: ADRUINO-NANO.D6, IO1.6
unnamed: ADRUINO-NANO.D7, IO1.5
unnamed: ADRUINO-NANO.D9, BUZZ.+ (1)
unnamed: -IN.1, DC-JACK.1, GND-IN.1, R2.1
unnamed: IO1.2, IO3.2
unnamed: 3.5MM.2, IO3.3, RJ45.3
unnamed: +IN.1, R1.2, VCC-O.1
VIDIN: IO1.1, MINIMOSD.VIDIN (VDIN)
VIDOUT: IO3.4, MINIMOSD.VIDOUT (VDOUT)

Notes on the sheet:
VO OSD
VO MAIN
VO DVR
GND
DVR Vin
DVR Vout
SDA (A4)
SCL (A6)
6:NC
5:AUD

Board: 2 copper layers, 20 parts (0 on the bottom side), 24 nets, no tracks yet.

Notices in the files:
parts and their libraries:
SparkFun-Connectors: Licensing: Creative Commons ShareAlike 4.0 International - https://creativecommons.org/licenses/by-sa/4.0
diy-modules: Released under the Creative Commons Attribution 4.0 International License: http://creativecommons.org/licenses/by/4.0
